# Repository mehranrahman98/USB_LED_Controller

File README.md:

# USB_LED_Controller
LED Controller made with KiCAD utilizing an STM32 ARM-based MCU.
 ## Schematic

 ## PCB

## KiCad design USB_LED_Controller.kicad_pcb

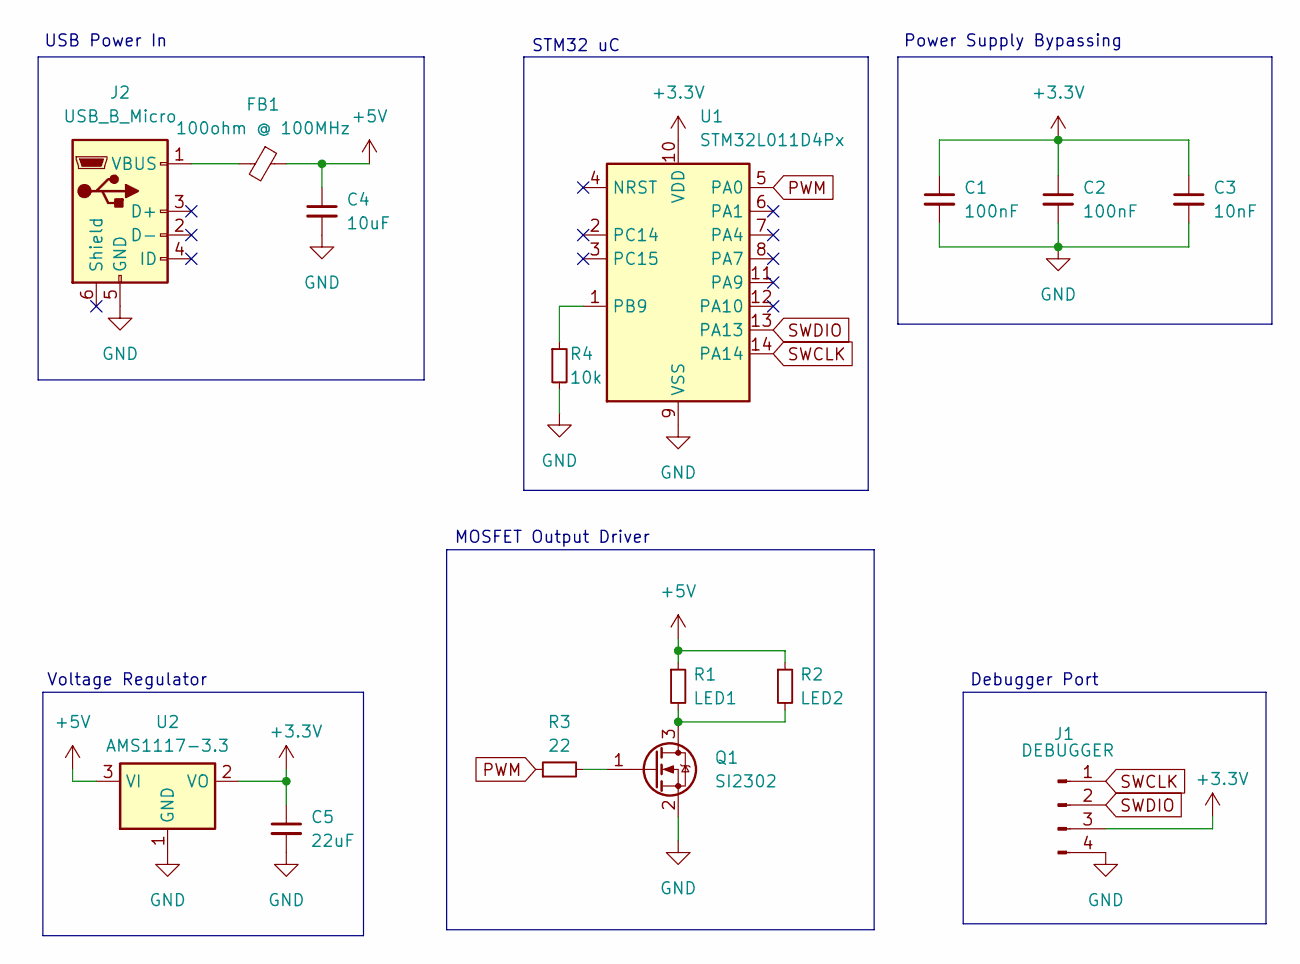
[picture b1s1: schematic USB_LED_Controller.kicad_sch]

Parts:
C1, C2: 100nF; C_0402_1005Metric
C3: 10nF; C_0402_1005Metric
C4: 10uF; C_0603_1608Metric
C5: 22uF; C_0603_1608Metric
FB1: 100ohm @ 100MHz; L_0805_2012Metric
J1: DEBUGGER; PinHeader_1x04_P1.27mm_Vertical
J2: USB_B_Micro; USB_Micro-B_Molex_47346-0001
Q1: SI2302; SOT-23
R1: LED1; R_0805_2012Metric
R2: LED2; R_0805_2012Metric
R3: 22; R_1206_3216Metric
R4: 10k; R_0805_2012Metric
U1: STM32L011D4Px; TSSOP-14_4.4x5mm_P0.65mm
U2: AMS1117-3.3; SOT-223-3_TabPin2

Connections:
+3.3V: C1.1, C2.1, C3.1, C5.1, J1.3, U1.10 (VDD), U2.2 (VO)
+5V: C4.1, FB1.1, R1.1, R2.1, U2.3 (VI)
GND: C1.2, C2.2, C3.2, C4.2, C5.2, J1.4, J2.5 (GND), Q1.2 (S), R4.2, U1.9 (VSS), U2.1 (GND)
unnamed: FB1.2, J2.1 (VBUS)
unnamed: Q1.3 (D), R1.2, R2.2
unnamed: Q1.1 (G), R3.2
unnamed: R4.1, U1.1 (PB9)
PWM: R3.1, U1.5 (PA0)
SWCLK: J1.1, U1.14 (PA14)
SWDIO: J1.2, U1.13 (PA13)

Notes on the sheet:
STM32 uC
Power Supply Bypassing
USB Power In
Voltage Regulator
MOSFET Output Driver
Debugger Port

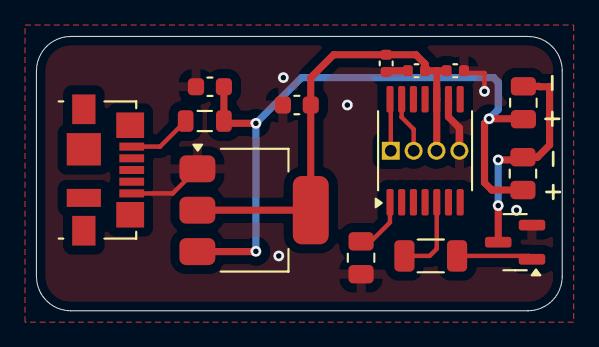
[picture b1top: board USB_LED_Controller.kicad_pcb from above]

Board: 2 copper layers, 29.2 x 15.2 mm, 15 parts (1 on the bottom side), 10 nets.

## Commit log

2025-01-05 Adding all files
